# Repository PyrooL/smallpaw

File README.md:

# Smallpaw

The Smallpaw is a 40% keyboard at heart, with the addition of a left-handed "Southpaw" numpad. CURRENTLY UNTESTED

[Original concept and build by /u/BubaThePig](https://www.reddit.com/r/MechanicalKeyboards/comments/95qxa0/made_my_first_keeb/), PyroL reached out to them asking to make a PCB for practice.

Latest render of PCB:

To-do:

- [ ] Mounting holes

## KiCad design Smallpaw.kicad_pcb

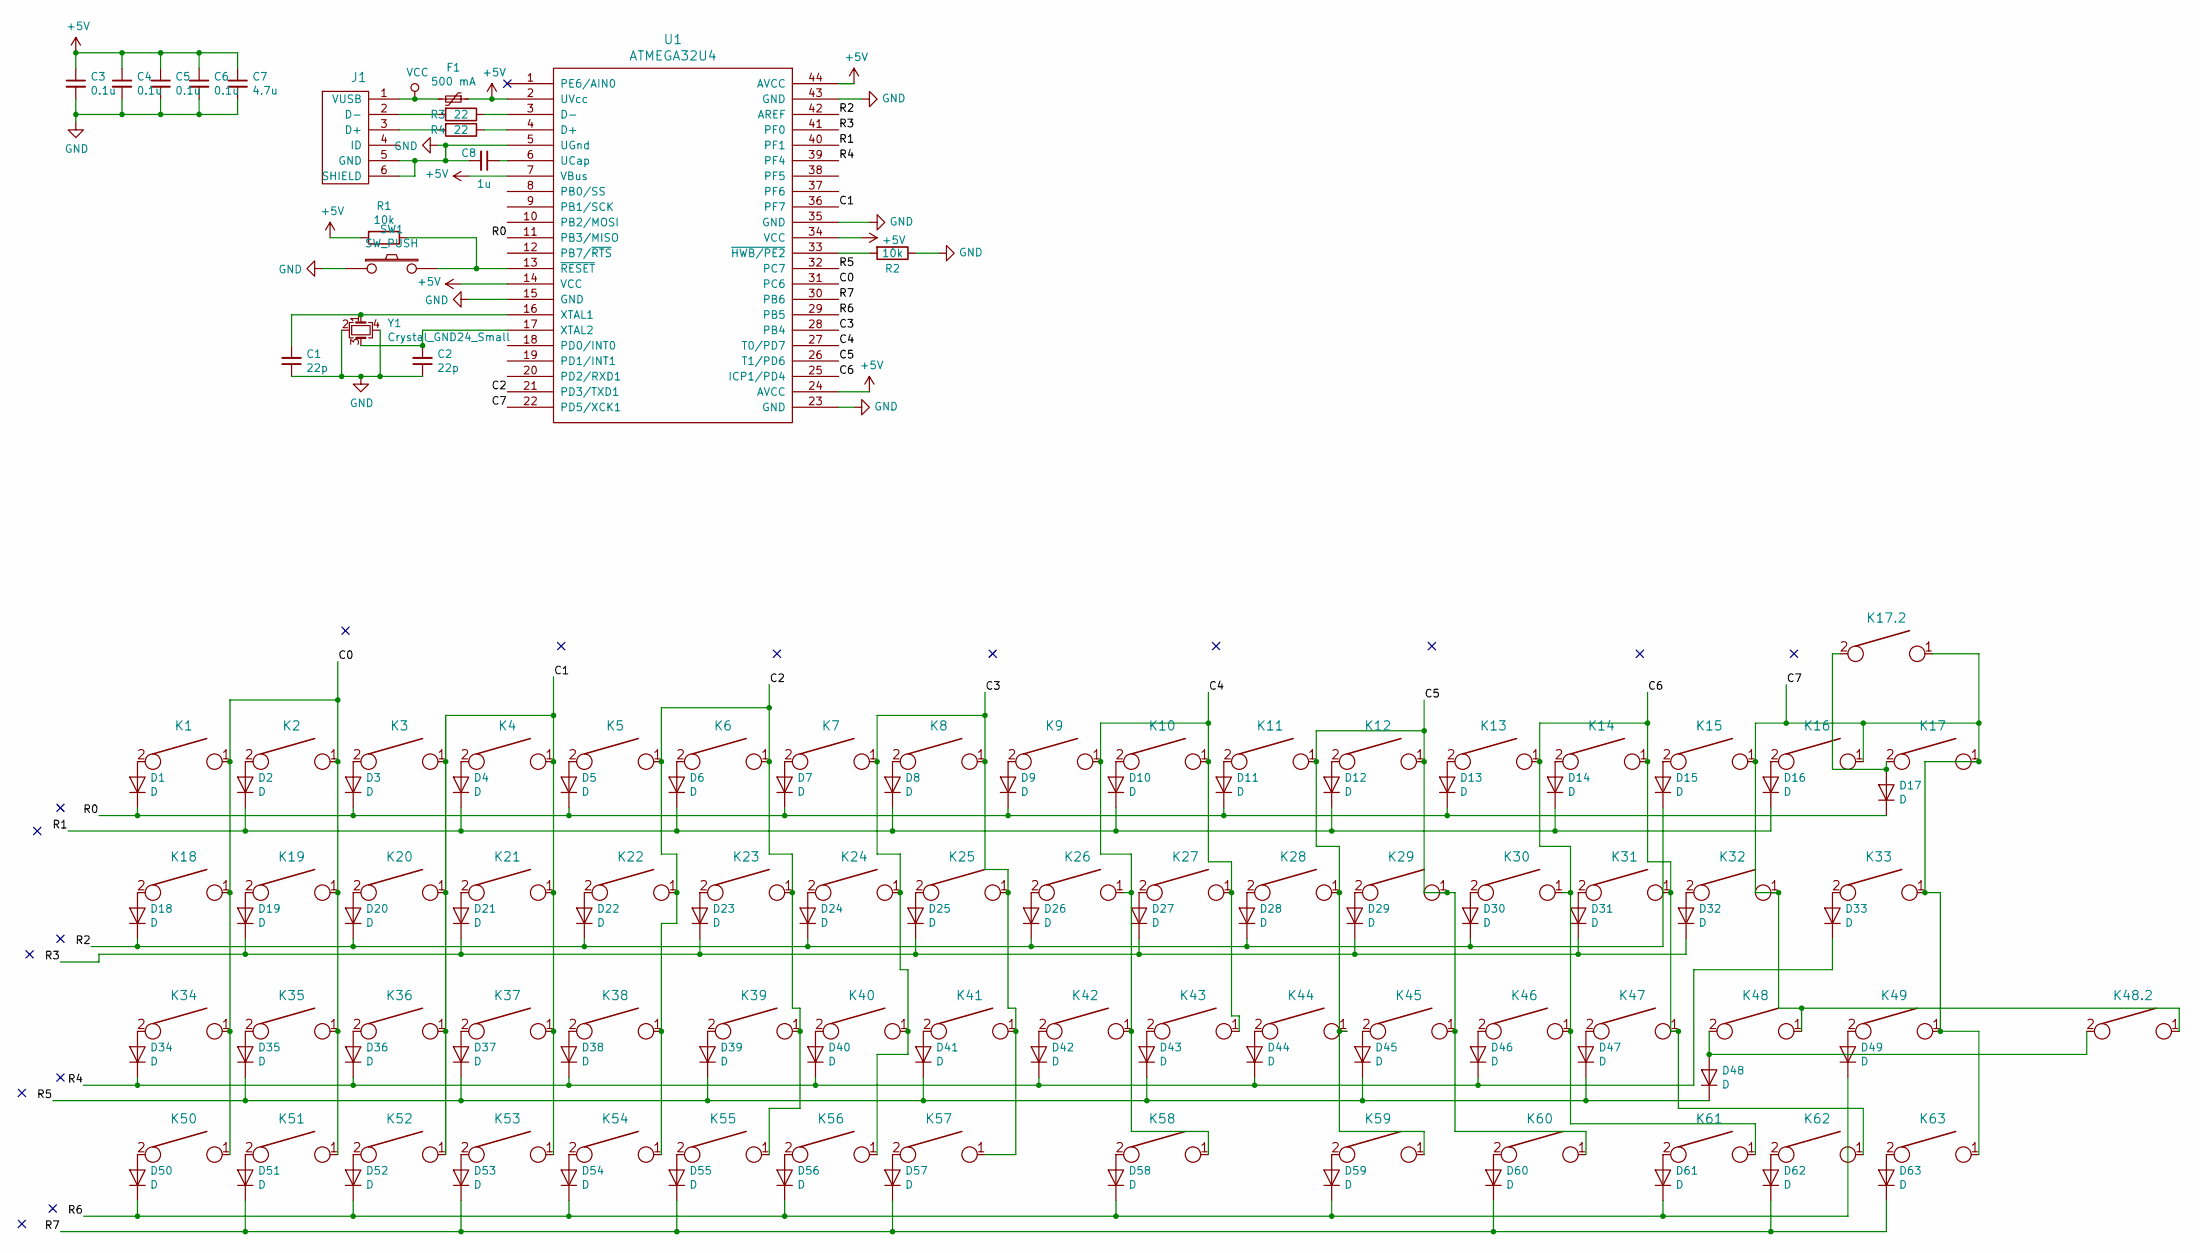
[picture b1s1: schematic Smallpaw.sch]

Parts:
C1, C2: 22p; C_0805_2012Metric_Pad1.15x1.40mm_HandSolder
C3, C4, C5, C6: 0.1u; C_0805_2012Metric_Pad1.15x1.40mm_HandSolder
C7: 4.7u; C_0805_2012Metric_Pad1.15x1.40mm_HandSolder
C8: 1u; C_0805_2012Metric_Pad1.15x1.40mm_HandSolder
D1, D2, D3, D4, D5, D6, D7, D8, D9, D10, D11, D12, D13, D14, D15, D16, D17, D18, D19, D20, D21, D22, D23, D24, D25, D26, D27, D28, D29, D30, D31, D32, D33, D34, D35, D36, D37, D38, D39, D40, D41, D42, D43, D44, D45, D46, D47, D48, D49, D50, D51, D52, D53, D54, D55, D56, D57, D58, D59, D60, D61, D62, D63: D; D_SOD-323
F1: 500 mA; Fuse_0805
J1: USB_mini_micro_B; USB-Mini-B_ LCSC-C46398
K1, K2, K3, K4, K5, K6, K7, K8, K9, K10, K11, K12, K13, K14, K15, K16, K17, K18, K19, K20, K21, K23, K24, K25, K26, K27, K28, K29, K30, K31, K32, K34, K35, K36, K37, K39, K40, K41, K42, K43, K44, K45, K46, K47, K49, K50, K51, K52, K53, K55, K56, K57, K60, K61, K62: KEYSW; MX-1U-NoLED
K17.2: KEYSW; MX-2U-NoLED
K22, K33: KEYSW; MX-1.5U-NoLED
K38: KEYSW; MX-1.75U-NoLED
K48, K54, K63: KEYSW; MX-1.25U-NoLED
K48.2, K58, K59: KEYSW; MX-2.25U-ReversedStabilizers-NoLED
R1, R2: 10k; R_0805_2012Metric_Pad1.15x1.40mm_HandSolder
R3, R4: 22; R_0805_2012Metric_Pad1.15x1.40mm_HandSolder
SW1: SW_PUSH; SW_SPST_SKQG
U1: ATMEGA32U4; TQFP-44_10x10mm_P0.8mm
Y1: Crystal_GND24_Small; Crystal_SMD_SeikoEpson_FA238-4pin_3.2x2.5mm

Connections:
+5V: C3.1, C4.1, C5.1, C6.1, C7.1, F1.1, R1.2, U1.2 (UVcc), U1.7 (VBus), U1.14 (VCC), U1.24 (AVCC), U1.34 (VCC), U1.44 (AVCC)
/C0: K1.1, K2.1, K18.1, K19.1, K34.1, K35.1, K50.1, K51.1, U1.31 (PC6)
/C1: K3.1, K4.1, K20.1, K21.1, K36.1, K37.1, K52.1, K53.1, U1.36 (PF7)
/C2: K5.1, K6.1, K22.1, K23.1, K38.1, K39.1, K54.1, K55.1, U1.21 (PD3/TXD1)
/C3: K7.1, K8.1, K24.1, K25.1, K40.1, K41.1, K56.1, K57.1, U1.28 (PB4)
/C4: K9.1, K10.1, K26.1, K27.1, K42.1, K43.1, K58.1, U1.27 (T0/PD7)
/C5: K11.1, K12.1, K28.1, K29.1, K44.1, K45.1, K59.1, K60.1, U1.26 (T1/PD6)
/C6: K13.1, K14.1, K30.1, K31.1, K46.1, K47.1, K61.1, K62.1, U1.25 (ICP1/PD4)
/C7: K15.1, K16.1, K17.1, K17.2.1, K32.1, K33.1, K48.1, K48.2.1, K49.1, K63.1, U1.22 (PD5/XCK1)
/R0: D1.1 (K), D3.1 (K), D5.1 (K), D7.1 (K), D9.1 (K), D11.1 (K), D13.1 (K), D17.1 (K), U1.11 (PB3/MISO)
/R1: D2.1 (K), D4.1 (K), D6.1 (K), D8.1 (K), D10.1 (K), D12.1 (K), D14.1 (K), D16.1 (K), U1.40 (PF1)
/R2: D15.1 (K), D18.1 (K), D20.1 (K), D22.1 (K), D24.1 (K), D26.1 (K), D28.1 (K), D30.1 (K), U1.42 (AREF)
/R3: D19.1 (K), D21.1 (K), D23.1 (K), D25.1 (K), D27.1 (K), D29.1 (K), D31.1 (K), D32.1 (K), U1.41 (PF0)
/R4: D33.1 (K), D34.1 (K), D36.1 (K), D38.1 (K), D40.1 (K), D42.1 (K), D44.1 (K), D46.1 (K), U1.39 (PF4)
/R5: D35.1 (K), D37.1 (K), D39.1 (K), D41.1 (K), D43.1 (K), D45.1 (K), D47.1 (K), D48.1 (K), U1.32 (PC7)
/R6: D49.1 (K), D50.1 (K), D52.1 (K), D54.1 (K), D56.1 (K), D58.1 (K), D59.1 (K), D61.1 (K), U1.29 (PB5)
/R7: D51.1 (K), D53.1 (K), D55.1 (K), D57.1 (K), D60.1 (K), D62.1 (K), D63.1 (K), U1.30 (PB6)
GND: C1.1, C2.1, C3.2, C4.2, C5.2, C6.2, C7.2, C8.2, J1.5 (GND), J1.6 (SHIELD), R2.1, SW1.1, U1.5 (UGnd), U1.15 (GND), U1.23 (GND), U1.35 (GND), U1.43 (GND), Y1.2, Y1.4
unnamed: C1.2, U1.16 (XTAL1), Y1.1
unnamed: C2.2, U1.17 (XTAL2), Y1.3
unnamed: C8.1, U1.6 (UCap)
unnamed: D1.2 (A), K1.2
unnamed: D2.2 (A), K2.2
unnamed: D3.2 (A), K3.2
unnamed: D4.2 (A), K4.2
unnamed: D5.2 (A), K5.2
unnamed: D6.2 (A), K6.2
unnamed: D7.2 (A), K7.2
unnamed: D8.2 (A), K8.2
unnamed: D9.2 (A), K9.2
unnamed: D10.2 (A), K10.2
unnamed: D11.2 (A), K11.2
unnamed: D12.2 (A), K12.2
unnamed: D13.2 (A), K13.2
unnamed: D14.2 (A), K14.2
unnamed: D15.2 (A), K15.2
unnamed: D16.2 (A), K16.2
unnamed: D17.2 (A), K17.2, K17.2.2
unnamed: D18.2 (A), K18.2
unnamed: D19.2 (A), K19.2
unnamed: D20.2 (A), K20.2
unnamed: D21.2 (A), K21.2
unnamed: D22.2 (A), K22.2
unnamed: D23.2 (A), K23.2
unnamed: D24.2 (A), K24.2
unnamed: D25.2 (A), K25.2
unnamed: D26.2 (A), K26.2
unnamed: D27.2 (A), K27.2
unnamed: D28.2 (A), K28.2
unnamed: D29.2 (A), K29.2
unnamed: D30.2 (A), K30.2
unnamed: D31.2 (A), K31.2
unnamed: D32.2 (A), K32.2
unnamed: D33.2 (A), K33.2
unnamed: D34.2 (A), K34.2
unnamed: D35.2 (A), K35.2
unnamed: D36.2 (A), K36.2
unnamed: D37.2 (A), K37.2
unnamed: D38.2 (A), K38.2
unnamed: D39.2 (A), K39.2
unnamed: D40.2 (A), K40.2
unnamed: D41.2 (A), K41.2
unnamed: D42.2 (A), K42.2
unnamed: D43.2 (A), K43.2
unnamed: D44.2 (A), K44.2
unnamed: D45.2 (A), K45.2
unnamed: D46.2 (A), K46.2
unnamed: D47.2 (A), K47.2
unnamed: D48.2 (A), K48.2, K48.2.2
unnamed: D49.2 (A), K49.2
unnamed: D50.2 (A), K50.2
unnamed: D51.2 (A), K51.2
unnamed: D52.2 (A), K52.2
unnamed: D53.2 (A), K53.2
unnamed: D54.2 (A), K54.2
unnamed: D55.2 (A), K55.2
unnamed: D56.2 (A), K56.2
unnamed: D57.2 (A), K57.2
unnamed: D58.2 (A), K58.2
unnamed: D59.2 (A), K59.2
unnamed: D60.2 (A), K60.2
unnamed: D61.2 (A), K61.2
unnamed: D62.2 (A), K62.2
unnamed: D63.2 (A), K63.2
unnamed: J1.2 (D-), R3.2
unnamed: J1.3 (D+), R4.2
unnamed: R1.1, SW1.2, U1.13 (~RESET)
unnamed: R2.2, U1.33 (~HWB/PE2)
unnamed: R3.1, U1.3 (D-)
unnamed: R4.1, U1.4 (D+)
VCC: F1.2, J1.1 (VUSB)

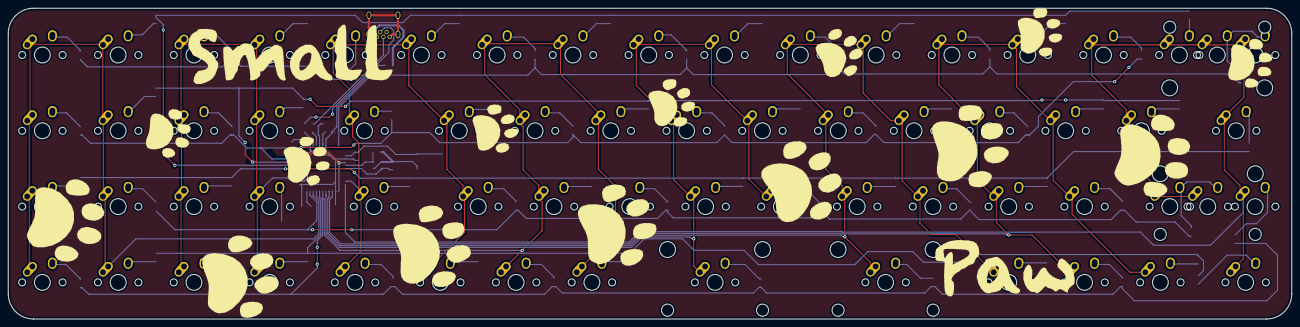
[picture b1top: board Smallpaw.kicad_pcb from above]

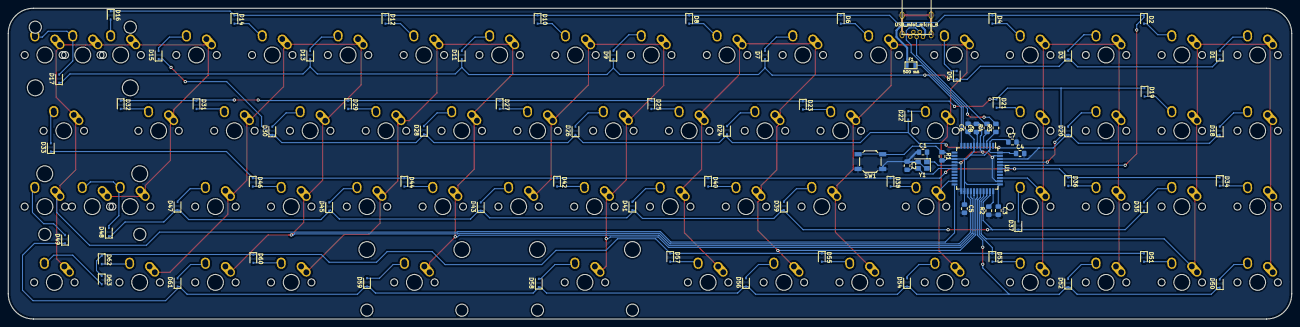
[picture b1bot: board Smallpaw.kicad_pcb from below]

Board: 2 copper layers, 322.6 x 78.1 mm, 145 parts (80 on the bottom side), 91 nets.

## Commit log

2018-09-18 readme
2018-10-15 formatting
2018-10-15 checkbox lol
2019-03-23 jaja blabla or ckck ckck
2020-03-18 routed rows/columns
2020-03-19 miniusb
